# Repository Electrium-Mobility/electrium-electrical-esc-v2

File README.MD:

Electrium ESC V2.0

This one uses an RP2040 and DRV8323 opposed to the previous STM32F407ZGT6 and DRV8301.
It features a lower cost, simpler components, and (hopefully) works better!

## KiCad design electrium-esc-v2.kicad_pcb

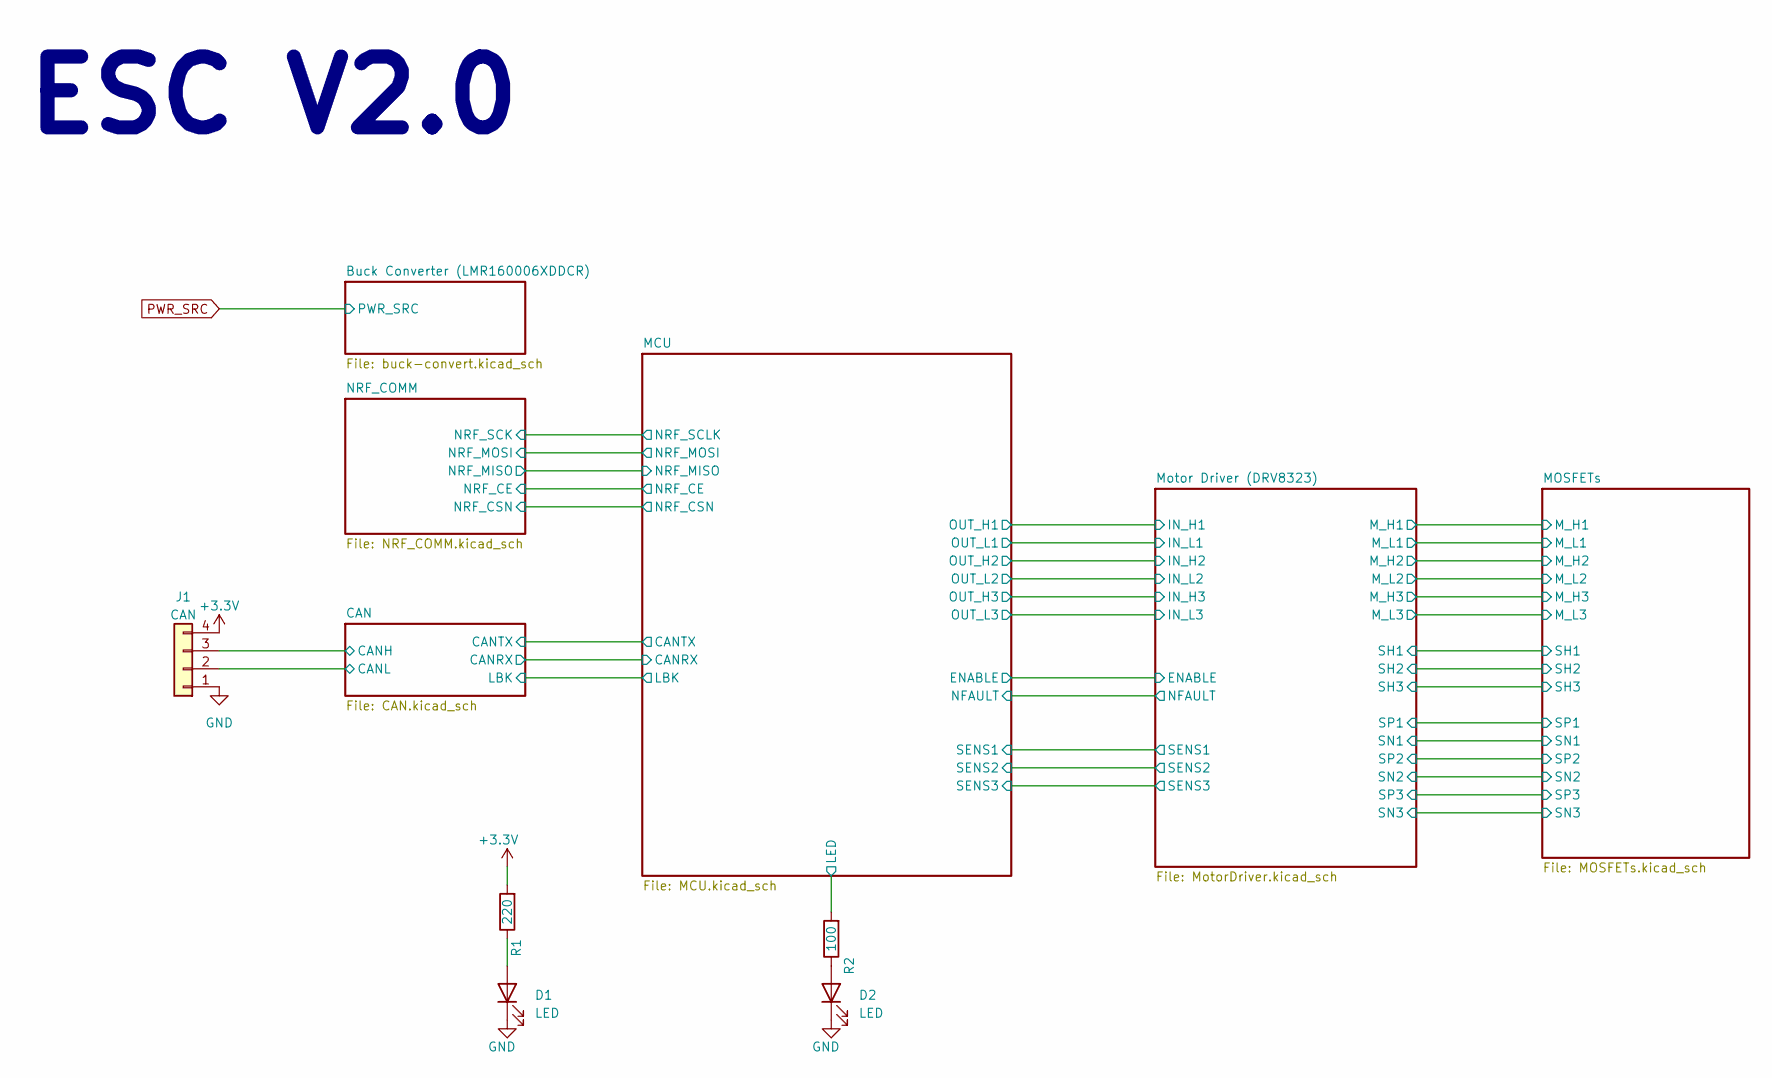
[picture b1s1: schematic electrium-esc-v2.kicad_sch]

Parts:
D1, D2: LED; D_0402_1005Metric
J1: CAN; JST_XH_B4B-XH-A_1x04_P2.50mm_Vertical
R1: 220; R_0603_1608Metric
R2: 100; R_0603_1608Metric

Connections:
/CAN/CAN+: J1.3; also elsewhere on the board
/CAN/CAN-: J1.2; also elsewhere on the board
/MCU/LED: R2.2; also elsewhere on the board
GND: D1.1 (K), D2.1 (K), J1.1; also elsewhere on the board
unnamed: D1.2 (A), R1.1
unnamed: D2.2 (A), R2.1

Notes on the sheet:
ESC V2.0

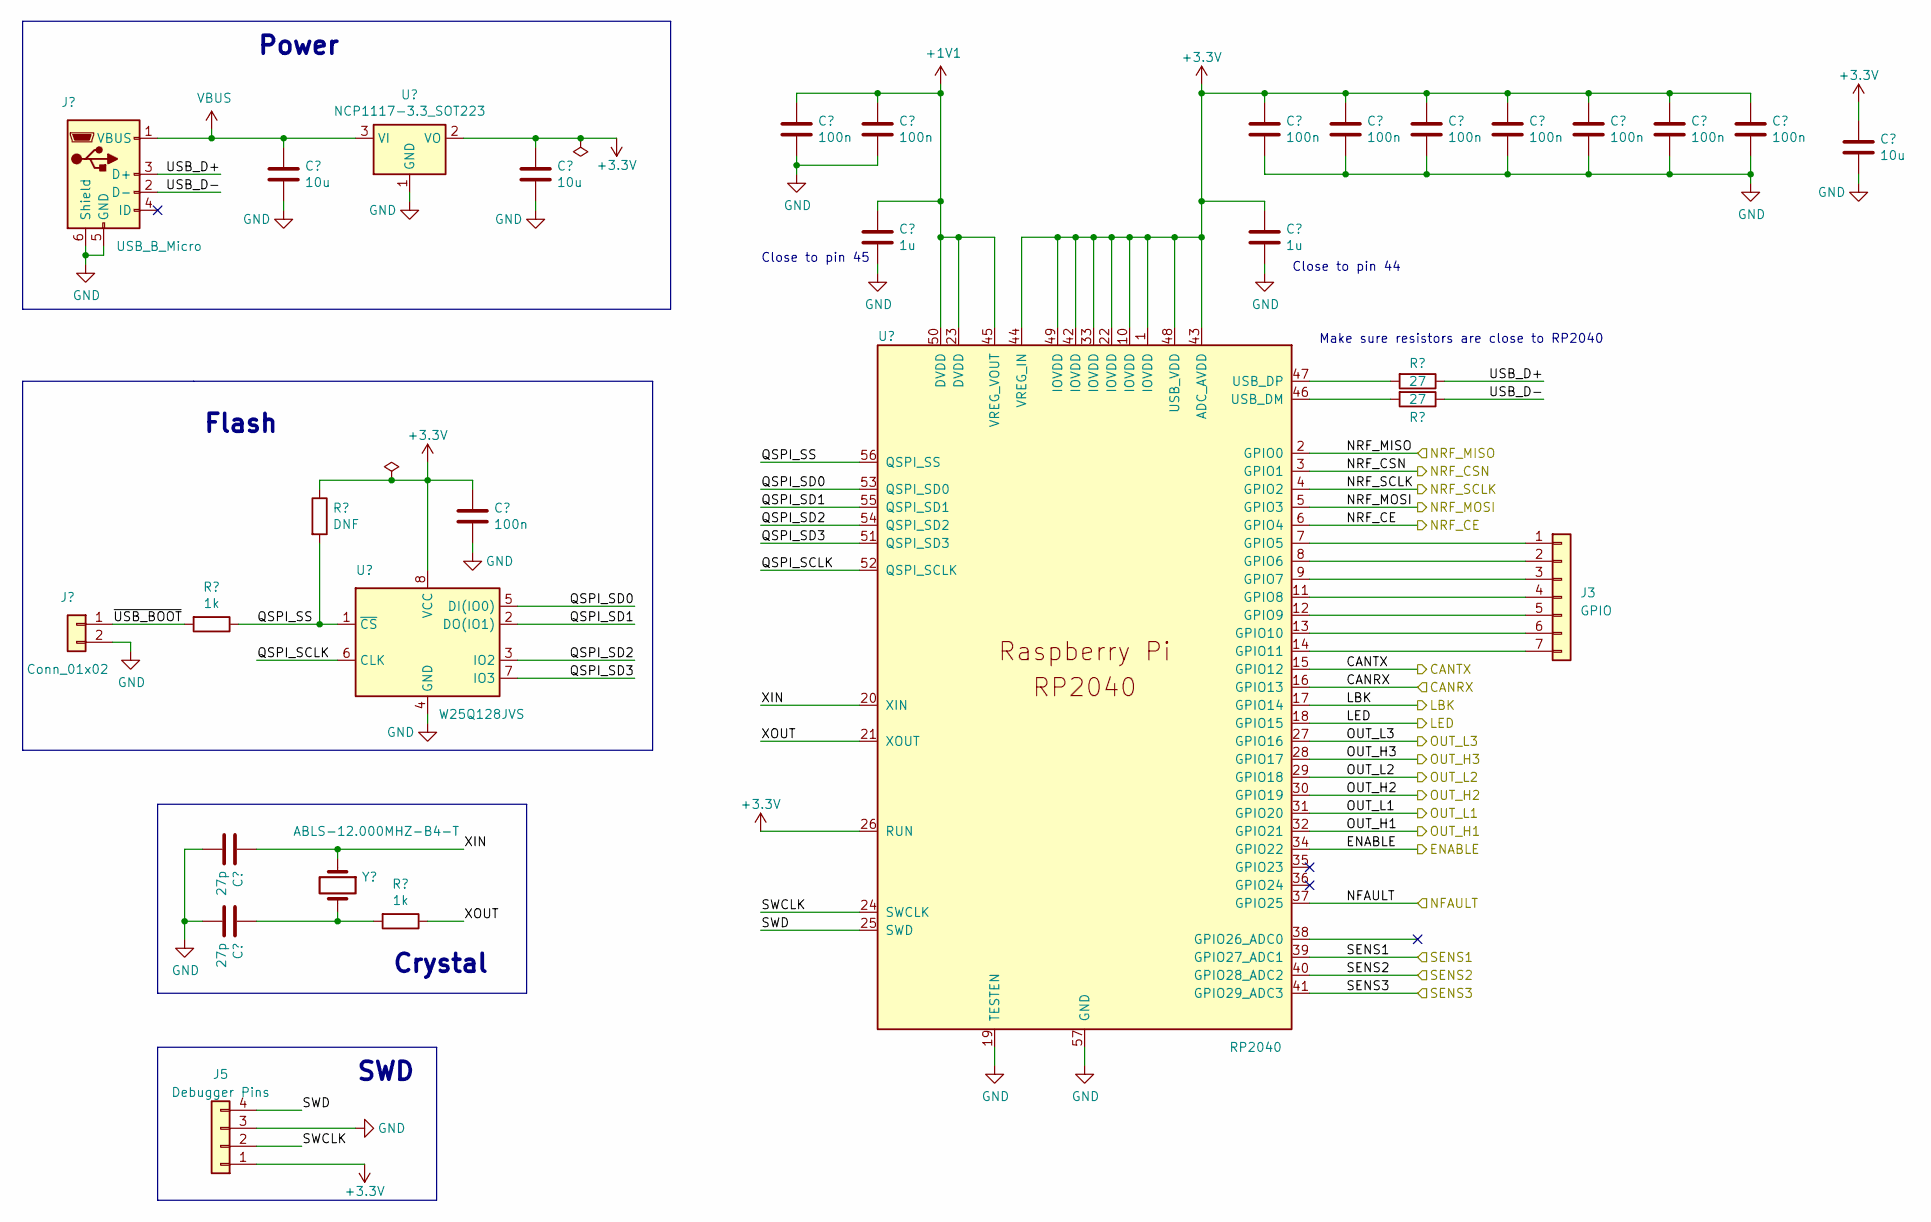
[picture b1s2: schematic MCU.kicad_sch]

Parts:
C1, C2, C3, C4, C5, C6, C7, C8, C9, C15: 100n; C_0603_1608Metric
C10: 10u; CP_Radial_D5.0mm_P2.50mm
C11, C12: 10u; C_0603_1608Metric
C13, C14: 1u; C_0603_1608Metric
C16, C17: 27p; C_0603_1608Metric
J2: USB_B_Micro; USB_Micro-B_Molex-105017-0001
J3: GPIO; PinSocket_1x07_P2.54mm_Vertical
J4: Conn_01x02; PinHeader_1x02_P2.54mm_Vertical
J5: Debugger Pins; JST_XH_B4B-XH-A_1x04_P2.50mm_Vertical
R3, R4: 27; R_0603_1608Metric
R5: DNF
R6, R7: 1k; R_0603_1608Metric
U1: NCP1117-3.3_SOT223; SOT-223-3_TabPin2
U2: W25Q128JVS; SOIC-8_5.23x5.23mm_P1.27mm
U3: RP2040; RP2040-QFN-56
Y1: ABLS-12.000MHZ-B4-T; Crystal_SMD_HC49-US

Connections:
+1V1: C1.1, C2.1, C13.1, U3.23 (DVDD), U3.45 (VREG_VOUT), U3.50 (DVDD)
/MCU/CANRX: U3.16 (GPIO13); also elsewhere on the board
/MCU/CANTX: U3.15 (GPIO12); also elsewhere on the board
/MCU/ENABLE: U3.34 (GPIO22); also elsewhere on the board
/MCU/LBK: U3.17 (GPIO14); also elsewhere on the board
/MCU/LED: U3.18 (GPIO15); also elsewhere on the board
/MCU/NFAULT: U3.37 (GPIO25); also elsewhere on the board
/MCU/NRF_CE: U3.6 (GPIO4); also elsewhere on the board
/MCU/NRF_CSN: U3.3 (GPIO1); also elsewhere on the board
/MCU/NRF_MISO: U3.2 (GPIO0); also elsewhere on the board
/MCU/NRF_MOSI: U3.5 (GPIO3); also elsewhere on the board
/MCU/NRF_SCLK: U3.4 (GPIO2); also elsewhere on the board
/MCU/OUT_H1: U3.32 (GPIO21); also elsewhere on the board
/MCU/OUT_H2: U3.30 (GPIO19); also elsewhere on the board
/MCU/OUT_H3: U3.28 (GPIO17); also elsewhere on the board
/MCU/OUT_L1: U3.31 (GPIO20); also elsewhere on the board
/MCU/OUT_L2: U3.29 (GPIO18); also elsewhere on the board
/MCU/OUT_L3: U3.27 (GPIO16); also elsewhere on the board
/MCU/QSPI_SCLK: U2.6 (CLK), U3.52 (QSPI_SCLK)
/MCU/QSPI_SD0: U2.5 (DI(IO0)), U3.53 (QSPI_SD0)
/MCU/QSPI_SD1: U2.2 (DO(IO1)), U3.55 (QSPI_SD1)
/MCU/QSPI_SD2: U2.3 (IO2), U3.54 (QSPI_SD2)
/MCU/QSPI_SD3: U2.7 (IO3), U3.51 (QSPI_SD3)
/MCU/QSPI_SS: R5.2, R6.1, U2.1 (~CS), U3.56 (QSPI_SS)
/MCU/SENS1: U3.39 (GPIO27_ADC1); also elsewhere on the board
/MCU/SENS2: U3.40 (GPIO28_ADC2); also elsewhere on the board
/MCU/SENS3: U3.41 (GPIO29_ADC3); also elsewhere on the board
/MCU/SWCLK: J5.2, U3.24 (SWCLK)
/MCU/SWD: J5.4, U3.25 (SWD)
/MCU/USB_D+: J2.3 (D+), R3.1
/MCU/USB_D-: J2.2 (D-), R4.1
/MCU/USB_DN: R4.2, U3.46 (USB_DM)
/MCU/USB_DP: R3.2, U3.47 (USB_DP)
/MCU/XIN: C16.1, U3.20 (XIN), Y1.1
/MCU/XOUT: R7.1, U3.21 (XOUT)
/MCU/~USB_BOOT: J4.1, R6.2
GND: C1.2, C2.2, C3.2, C4.2, C5.2, C6.2, C7.2, C8.2, C9.2, C10.2, C11.2, C12.2, C13.2, C14.2, C15.2, C16.2, C17.2, J2.5 (GND), J2.6 (Shield), J4.2, J5.3, U1.1 (GND), U2.4 (GND), U3.19 (TESTEN), U3.57 (GND); also elsewhere on the board
unnamed: C17.1, R7.2, Y1.2
unnamed: J3.1, U3.7 (GPIO5)
unnamed: J3.2, U3.8 (GPIO6)
unnamed: J3.3, U3.9 (GPIO7)
unnamed: J3.4, U3.11 (GPIO8)
unnamed: J3.5, U3.12 (GPIO9)
unnamed: J3.6, U3.13 (GPIO10)
unnamed: J3.7, U3.14 (GPIO11)
VBUS: C11.1, J2.1 (VBUS), U1.3 (VI)

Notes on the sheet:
SWD
Close to pin 44
Flash
Close to pin 45
Crystal
Make sure resistors are close to RP2040
Power

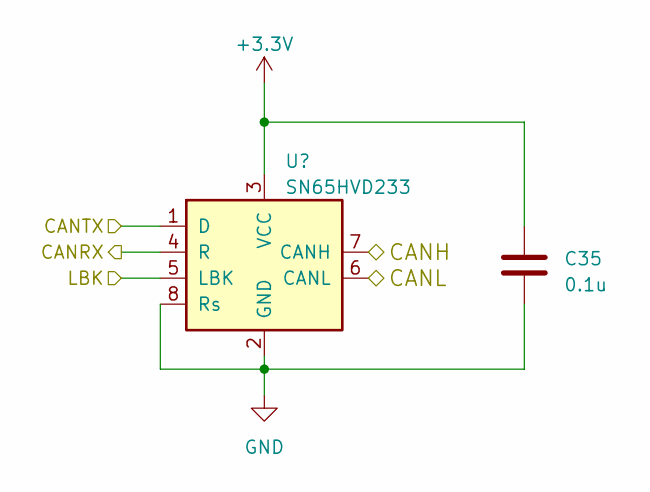
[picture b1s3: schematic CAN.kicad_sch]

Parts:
C35: 0.1u; C_0603_1608Metric
U6: SN65HVD233; SOIC-8_3.9x4.9mm_P1.27mm

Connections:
/CAN/CAN+: U6.6 (CANL); also elsewhere on the board
/CAN/CAN-: U6.7 (CANH); also elsewhere on the board
/MCU/CANRX: U6.4 (R); also elsewhere on the board
/MCU/CANTX: U6.1 (D); also elsewhere on the board
/MCU/LBK: U6.5 (LBK); also elsewhere on the board
GND: C35.2, U6.2 (GND), U6.8 (Rs); also elsewhere on the board

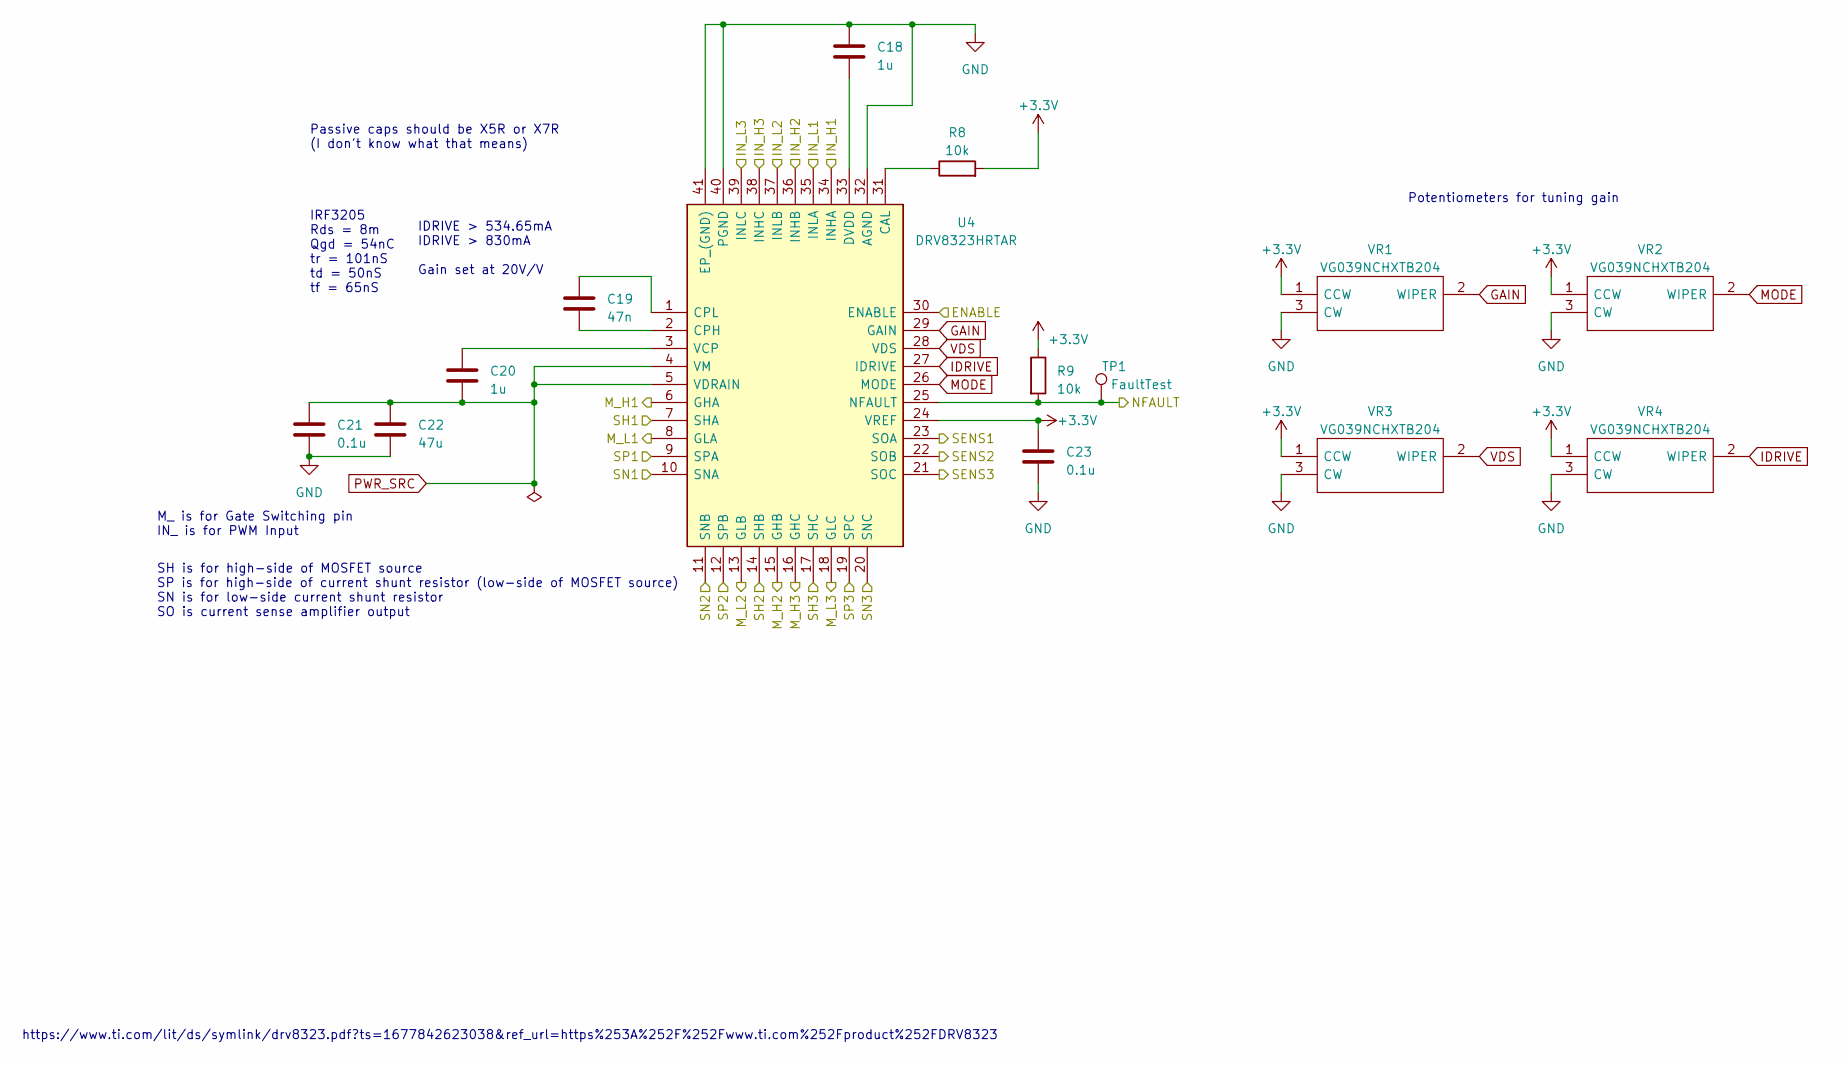
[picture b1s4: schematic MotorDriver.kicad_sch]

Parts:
C18, C20: 1u; C_0603_1608Metric
C19: 47n; C_0603_1608Metric
C21, C23: 0.1u; C_0603_1608Metric
C22: 47u; CP_Radial_D4.0mm_P1.50mm
R8, R9: 10k; R_0603_1608Metric
TP1: FaultTest
U4: DRV8323HRTAR; QFN50P600X600X80-41N-D; Manufacturer_Part_Number DRV8323HRTAR; Mouser Part Number 595-DRV8323HRTAR
VR1, VR2, VR3, VR4: VG039NCHXTB204; Manufacturer_Part_Number VG039NCHXTB204

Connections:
/MCU/ENABLE: U4.30 (ENABLE); also elsewhere on the board
/MCU/NFAULT: R9.2, TP1.1, U4.25 (NFAULT); also elsewhere on the board
/MCU/OUT_H1: U4.34 (INHA); also elsewhere on the board
/MCU/OUT_H2: U4.36 (INHB); also elsewhere on the board
/MCU/OUT_H3: U4.38 (INHC); also elsewhere on the board
/MCU/OUT_L1: U4.35 (INLA); also elsewhere on the board
/MCU/OUT_L2: U4.37 (INLB); also elsewhere on the board
/MCU/OUT_L3: U4.39 (INLC); also elsewhere on the board
/MCU/SENS1: U4.23 (SOA); also elsewhere on the board
/MCU/SENS2: U4.22 (SOB); also elsewhere on the board
/MCU/SENS3: U4.21 (SOC); also elsewhere on the board
/MOSFETs/M_H1: U4.6 (GHA); also elsewhere on the board
/MOSFETs/M_H2: U4.15 (GHB); also elsewhere on the board
/MOSFETs/M_H3: U4.16 (GHC); also elsewhere on the board
/MOSFETs/M_L1: U4.8 (GLA); also elsewhere on the board
/MOSFETs/M_L2: U4.13 (GLB); also elsewhere on the board
/MOSFETs/M_L3: U4.18 (GLC); also elsewhere on the board
/MOSFETs/SH1: U4.7 (SHA); also elsewhere on the board
/MOSFETs/SH2: U4.14 (SHB); also elsewhere on the board
/MOSFETs/SH3: U4.17 (SHC); also elsewhere on the board
/MOSFETs/SP1: U4.9 (SPA); also elsewhere on the board
/MOSFETs/SP2: U4.12 (SPB); also elsewhere on the board
/MOSFETs/SP3: U4.19 (SPC); also elsewhere on the board
GAIN: U4.29 (GAIN), VR1.2 (WIPER)
GND: C18.2, C21.2, C22.2, C23.2, U4.10 (SNA), U4.11 (SNB), U4.20 (SNC), U4.32 (AGND), U4.40 (PGND), U4.41 (EP_(GND)), VR1.3 (CW), VR2.3 (CW), VR3.3 (CW), VR4.3 (CW); also elsewhere on the board
IDRIVE: U4.27 (IDRIVE), VR4.2 (WIPER)
MODE: U4.26 (MODE), VR2.2 (WIPER)
unnamed: R8.1, U4.31 (CAL)
unnamed: C19.2, U4.2 (CPH)
unnamed: C19.1, U4.1 (CPL)
unnamed: C18.1, U4.33 (DVDD)
unnamed: C20.1, U4.3 (VCP)
PWR_SRC: C20.2, C21.1, C22.1, U4.4 (VM), U4.5 (VDRAIN); also elsewhere on the board
VDS: U4.28 (VDS), VR3.2 (WIPER)

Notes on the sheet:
IDRIVE > 534.65mA IDRIVE > 830mA Gain set at 20V/V
SH is for high-side of MOSFET source SP is for high-side of current shunt resistor (low-side of MOSFET source) SN is for low-side current shunt resistor SO is current sense amplifier output
Potentiometers for tuning gain
Passive caps should be X5R or X7R (I don't know what that means)
https://www.ti.com/lit/ds/symlink/drv8323.pdf?ts=1677842623038&ref_url=https%253A%252F%252Fwww.ti.com%252Fproduct%252FDRV8323
M_ is for Gate Switching pin IN_ is for PWM Input
IRF3205 Rds = 8m Qgd = 54nC tr = 101nS td = 50nS tf = 65nS

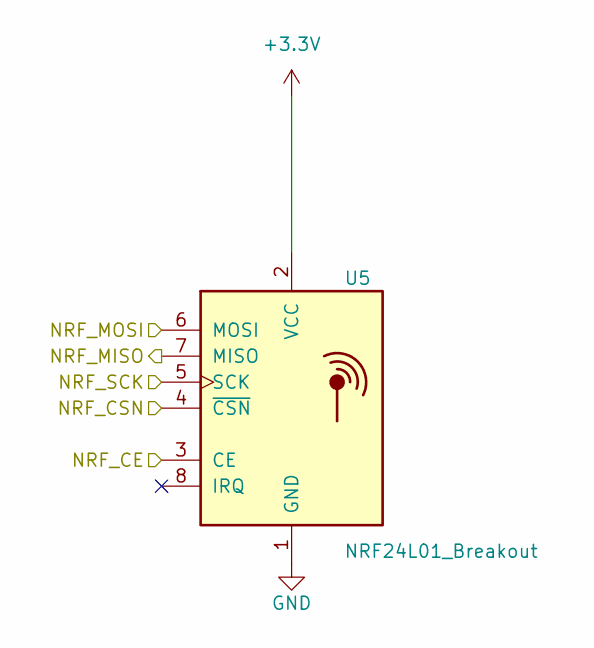
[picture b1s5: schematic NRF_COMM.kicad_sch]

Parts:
U5: NRF24L01_Breakout; nRF24L01_Breakout

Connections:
/MCU/NRF_CE: U5.3 (CE); also elsewhere on the board
/MCU/NRF_CSN: U5.4 (~CSN); also elsewhere on the board
/MCU/NRF_MISO: U5.7 (MISO); also elsewhere on the board
/MCU/NRF_MOSI: U5.6 (MOSI); also elsewhere on the board
/MCU/NRF_SCLK: U5.5 (SCK); also elsewhere on the board
GND: U5.1 (GND); also elsewhere on the board

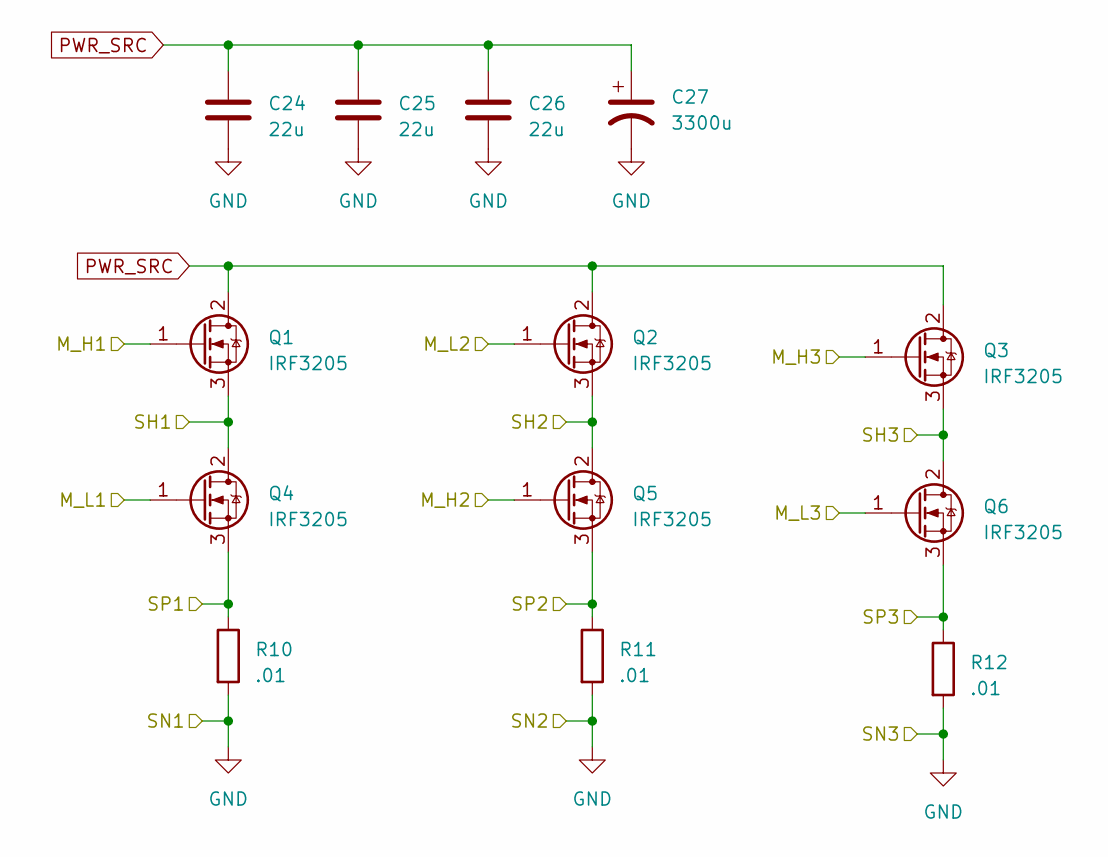
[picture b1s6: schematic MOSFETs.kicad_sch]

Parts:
C24, C25, C26: 22u; CP_Elec_6.3x7.7
C27: 3300u; CP_Radial_D22.0mm_P10.00mm_SnapIn
Q1, Q2, Q3, Q4, Q5, Q6: IRF3205; TO-220-3_Vertical
R10, R11, R12: .01; R_2512_6332Metric_Pad1.40x3.35mm_HandSolder

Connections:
/MOSFETs/M_H1: Q1.1 (G); also elsewhere on the board
/MOSFETs/M_H2: Q5.1 (G); also elsewhere on the board
/MOSFETs/M_H3: Q3.1 (G); also elsewhere on the board
/MOSFETs/M_L1: Q4.1 (G); also elsewhere on the board
/MOSFETs/M_L2: Q2.1 (G); also elsewhere on the board
/MOSFETs/M_L3: Q6.1 (G); also elsewhere on the board
/MOSFETs/SH1: Q1.3 (S), Q4.2 (D); also elsewhere on the board
/MOSFETs/SH2: Q2.3 (S), Q5.2 (D); also elsewhere on the board
/MOSFETs/SH3: Q3.3 (S), Q6.2 (D); also elsewhere on the board
/MOSFETs/SP1: Q4.3 (S), R10.1; also elsewhere on the board
/MOSFETs/SP2: Q5.3 (S), R11.1; also elsewhere on the board
/MOSFETs/SP3: Q6.3 (S), R12.1; also elsewhere on the board
GND: C24.2, C25.2, C26.2, C27.2, R10.2, R11.2, R12.2; also elsewhere on the board
PWR_SRC: C24.1, C25.1, C26.1, C27.1, Q1.2 (D), Q2.2 (D), Q3.2 (D); also elsewhere on the board

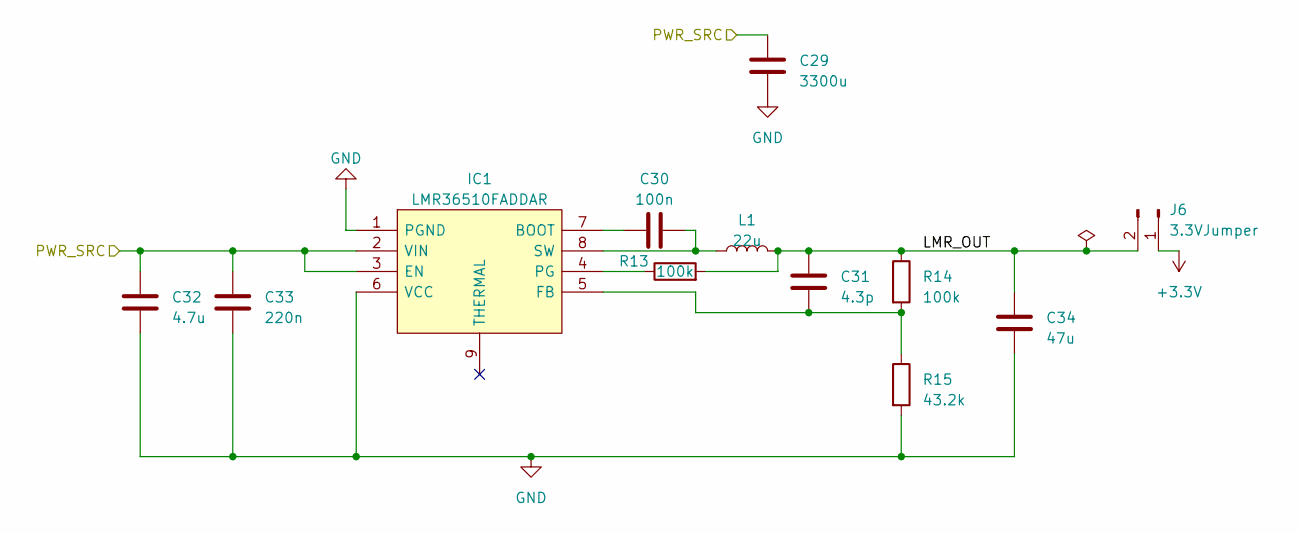
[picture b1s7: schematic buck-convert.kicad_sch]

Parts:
C29: 3300u
C30: 100n; C_0603_1608Metric
C31: 4.3p; C_0603_1608Metric
C32: 4.7u; C_0603_1608Metric
C33: 220n; C_0603_1608Metric
C34: 47u; C_0603_1608Metric
IC1: LMR36510FADDAR; SOIC127P600X170-9N; Manufacturer_Part_Number LMR36510FADDAR; Mouser Part Number 595-LMR36510FADDAR
J6: 3.3VJumper; PinHeader_1x02_P2.54mm_Vertical
L1: 22u; L_Taiyo-Yuden_NR-30xx
R13, R14: 100k; R_0603_1608Metric
R15: 43.2k; R_0603_1608Metric

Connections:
GND: C29.2, C32.2, C33.2, C34.1, IC1.1 (PGND), IC1.6 (VCC), R15.2; also elsewhere on the board
unnamed: C30.1, IC1.7 (BOOT)
unnamed: C31.1, IC1.5 (FB), R14.2, R15.1
unnamed: IC1.4 (PG), R13.1
unnamed: C30.2, IC1.8 (SW), L1.1
PWR_SRC: C29.1, C32.1, C33.1, IC1.2 (VIN), IC1.3 (EN); also elsewhere on the board

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
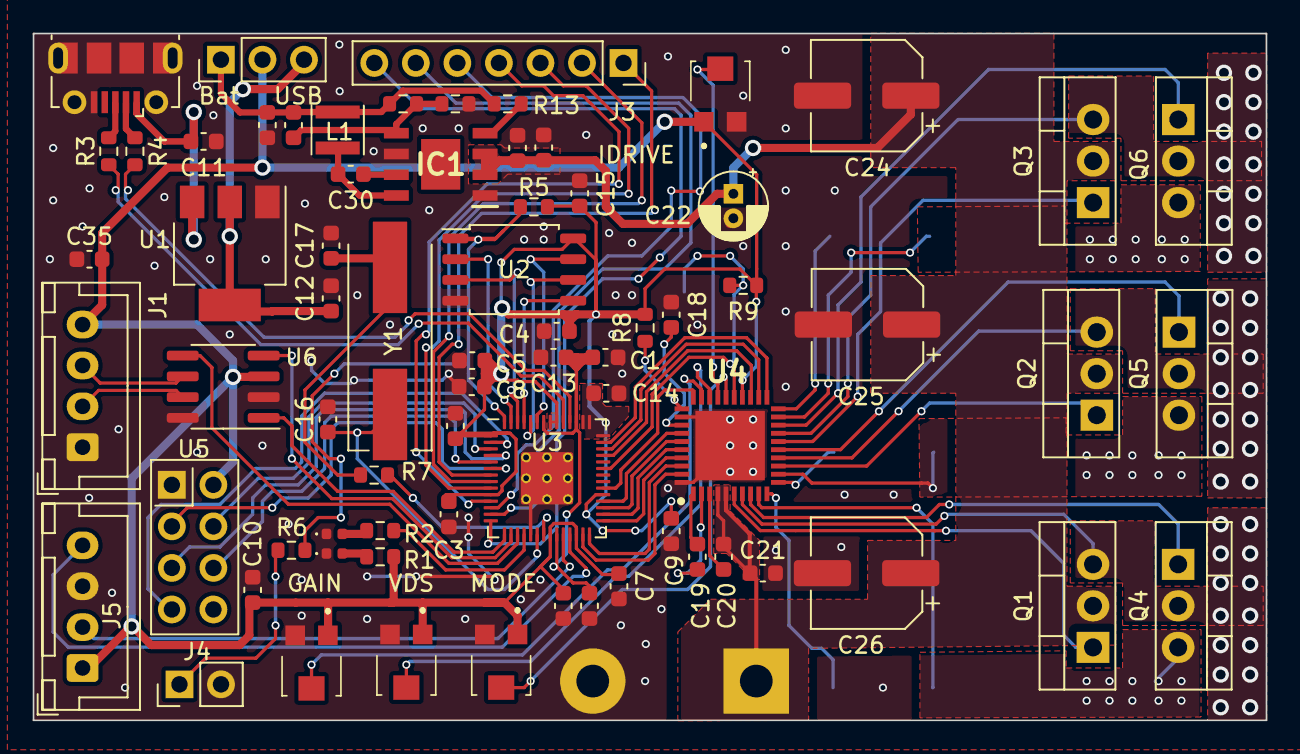
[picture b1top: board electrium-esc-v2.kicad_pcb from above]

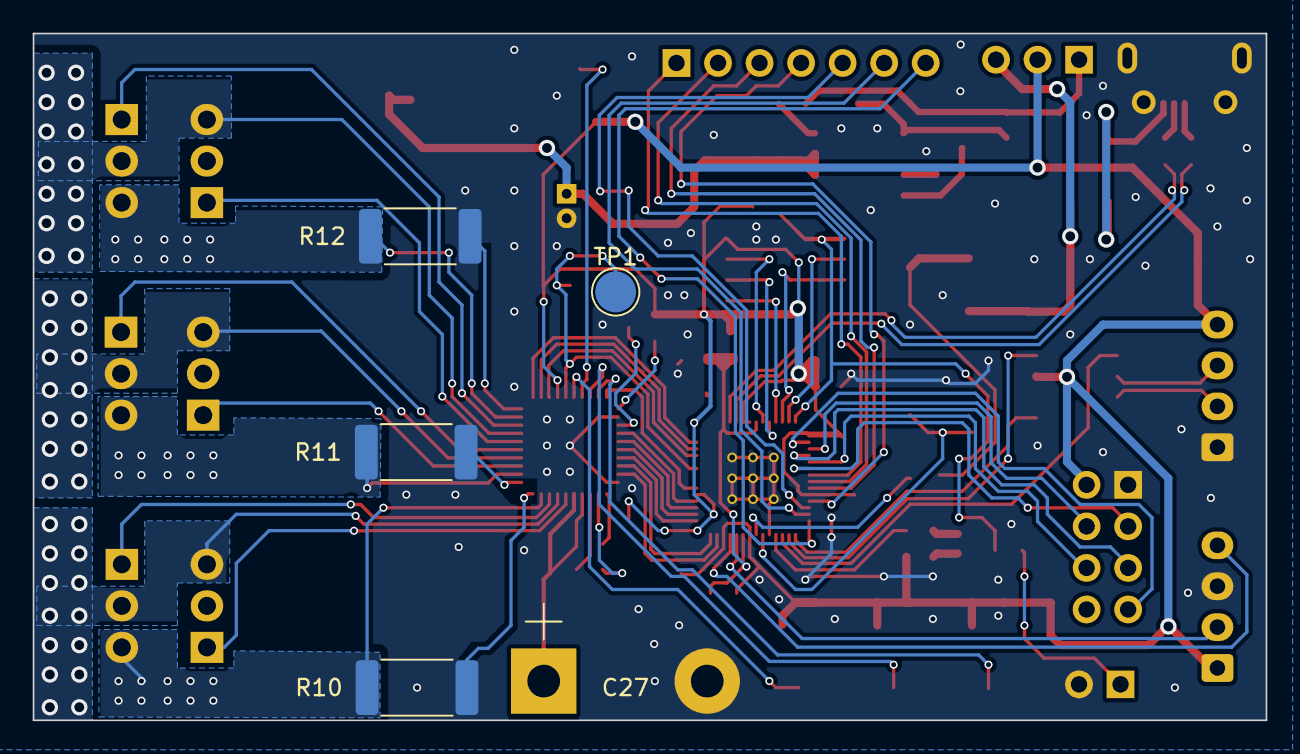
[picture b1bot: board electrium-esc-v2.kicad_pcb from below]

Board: 2 copper layers, 75.4 x 42.0 mm, 76 parts (5 on the bottom side), 79 nets.

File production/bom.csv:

Designator,Footprint,Quantity,Value,LCSC Part #
C1,0603,1,100n,
C10,0603,1,10u,
C11,0603,1,10u,
C12,0603,1,10u,
C13,0603,1,1u,
C14,0603,1,1u,
C15,0603,1,100n,
C16,0603,1,27p,
C17,0603,1,27p,
C18,0603,1,1u,
C19,0603,1,47n,
C2,0603,1,100n,
C20,0603,1,1u,
C21,0603,1,0.1u,
C22,CP_Radial_D4.0mm_P1.50mm,1,47u,
C23,0603,1,0.1u,
"C24, C25, C26",CP_Elec_6.3x7.7,3,22u,
C27,CP_Radial_D22.0mm_P10.00mm_SnapIn,1,3300u,
C3,0603,1,100n,
C30,0603,1,100n,
C31,0603,1,4.3p,
C32,0603,1,4.7u,
C33,0603,1,220n,
C34,0603,1,47u,
C35,0603,1,0.1u,
C4,0603,1,100n,
C5,0603,1,100n,
C6,0603,1,100n,
C7,0603,1,100n,
C8,0603,1,100n,
C9,0603,1,100n,
D1,0402,1,LED,
D2,0402,1,LED,
IC1,SOIC127P600X170-9N,1,LMR36510FADDAR,
J1,JST_XH_B4B-XH-A_1x04_P2.50mm_Vertical,1,CAN,
J2,USB_Micro-B_Molex-105017-0001,1,USB_B_Micro,
J3,PinSocket_1x07_P2.54mm_Vertical,1,GPIO,
J4,PinHeader_1x02_P2.54mm_Vertical,1,Conn_01x02,
J5,JST_XH_B4B-XH-A_1x04_P2.50mm_Vertical,1,Debugger Pins,
J6,PinHeader_1x03_P2.54mm_Vertical,1,Conn_01x03_Pin,
L1,L_Taiyo-Yuden_NR-30xx,1,22u,
"Q1, Q2, Q3, Q4, Q5, Q6",TO-220-3_Vertical,6,IRF3205,
R1,0603,1,220,
R10,2512,1,.01,
R11,2512,1,.01,
R12,2512,1,.01,
R13,0603,1,100k,
R14,0603,1,100k,
R15,0603,1,43.2k,
R2,0603,1,100,
R3,0603,1,27,
R4,0603,1,27,
R5,0603,1,DNF,
R6,0603,1,1k,
R7,0603,1,1k,
R8,0603,1,10k,
R9,0603,1,10k,
TP1,TestPoint_Pad_D2.5mm,1,FaultTest,
U1,SOT-223-3_TabPin2,1,NCP1117-3.3_SOT223,
U2,SOIC-8_5.23x5.23mm_P1.27mm,1,W25Q128JVS,
U3,RP2040-QFN-56,1,RP2040,
U4,QFN50P600X600X80-41N-D,1,DRV8323HRTAR,
U5,nRF24L01_Breakout,1,NRF24L01_Breakout,
U6,SOIC-8_3.9x4.9mm_P1.27mm,1,SN65HVD233,
"VR1, VR2, VR3, VR4",VG039NCHXTB204,4,VG039NCHXTB204,
Y1,Crystal_SMD_HC49-US,1,ABLS-12.000MHZ-B4-T,

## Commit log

2023-03-04 Add base files
2023-03-04 moved folder out
2023-03-04 ignore auto save cache
2023-03-04 changes to files
2023-03-04 removed backup git commit
2023-03-04 Add MotorDriver schematic sheet
2023-03-04 Add original files
2023-03-04 Add all connections
2023-03-04 Add CAN bus
2023-03-04 Remove dup folder
2023-03-04 Add buck converter schematic
2023-03-04 Additional renaming
2023-03-04 Fix a few errors
2023-03-04 Add buck converter
2023-03-04 Add reference changes
2023-03-04 Idk what this is but it's useful
2023-03-04 changed pins
2023-03-04 Re-annotate all sheets
2023-03-04 Re-annotate all components
2023-03-04 added nets to high level circuit
2023-03-04 Add proper footprints
2023-03-04 Add proper JST Connector
2023-03-04 fix ERC
2023-03-04 fixed ERC violations
2023-03-04 Fixed stuff
2023-03-05 Final schematic with no DRC errors
2023-03-05 Add final pads
2023-03-05 pcb designed
2023-03-05 first pcb design
2023-03-05 fixed shunt resistor traces
2023-03-05 minor improvements
2023-03-05 minor changes
2023-03-05 Add better traces
2023-03-05 Add production files
2023-03-05 Fix traces
2023-03-05 Add CAN bus thicker traces
2023-03-05 Add more trace width
2023-03-05 Final PCB V2
2023-03-05 Increase trace width
2023-03-05 added more spacing
2023-03-21 Switch M_H2 and M_L2
    Wrong gate pins were connected
